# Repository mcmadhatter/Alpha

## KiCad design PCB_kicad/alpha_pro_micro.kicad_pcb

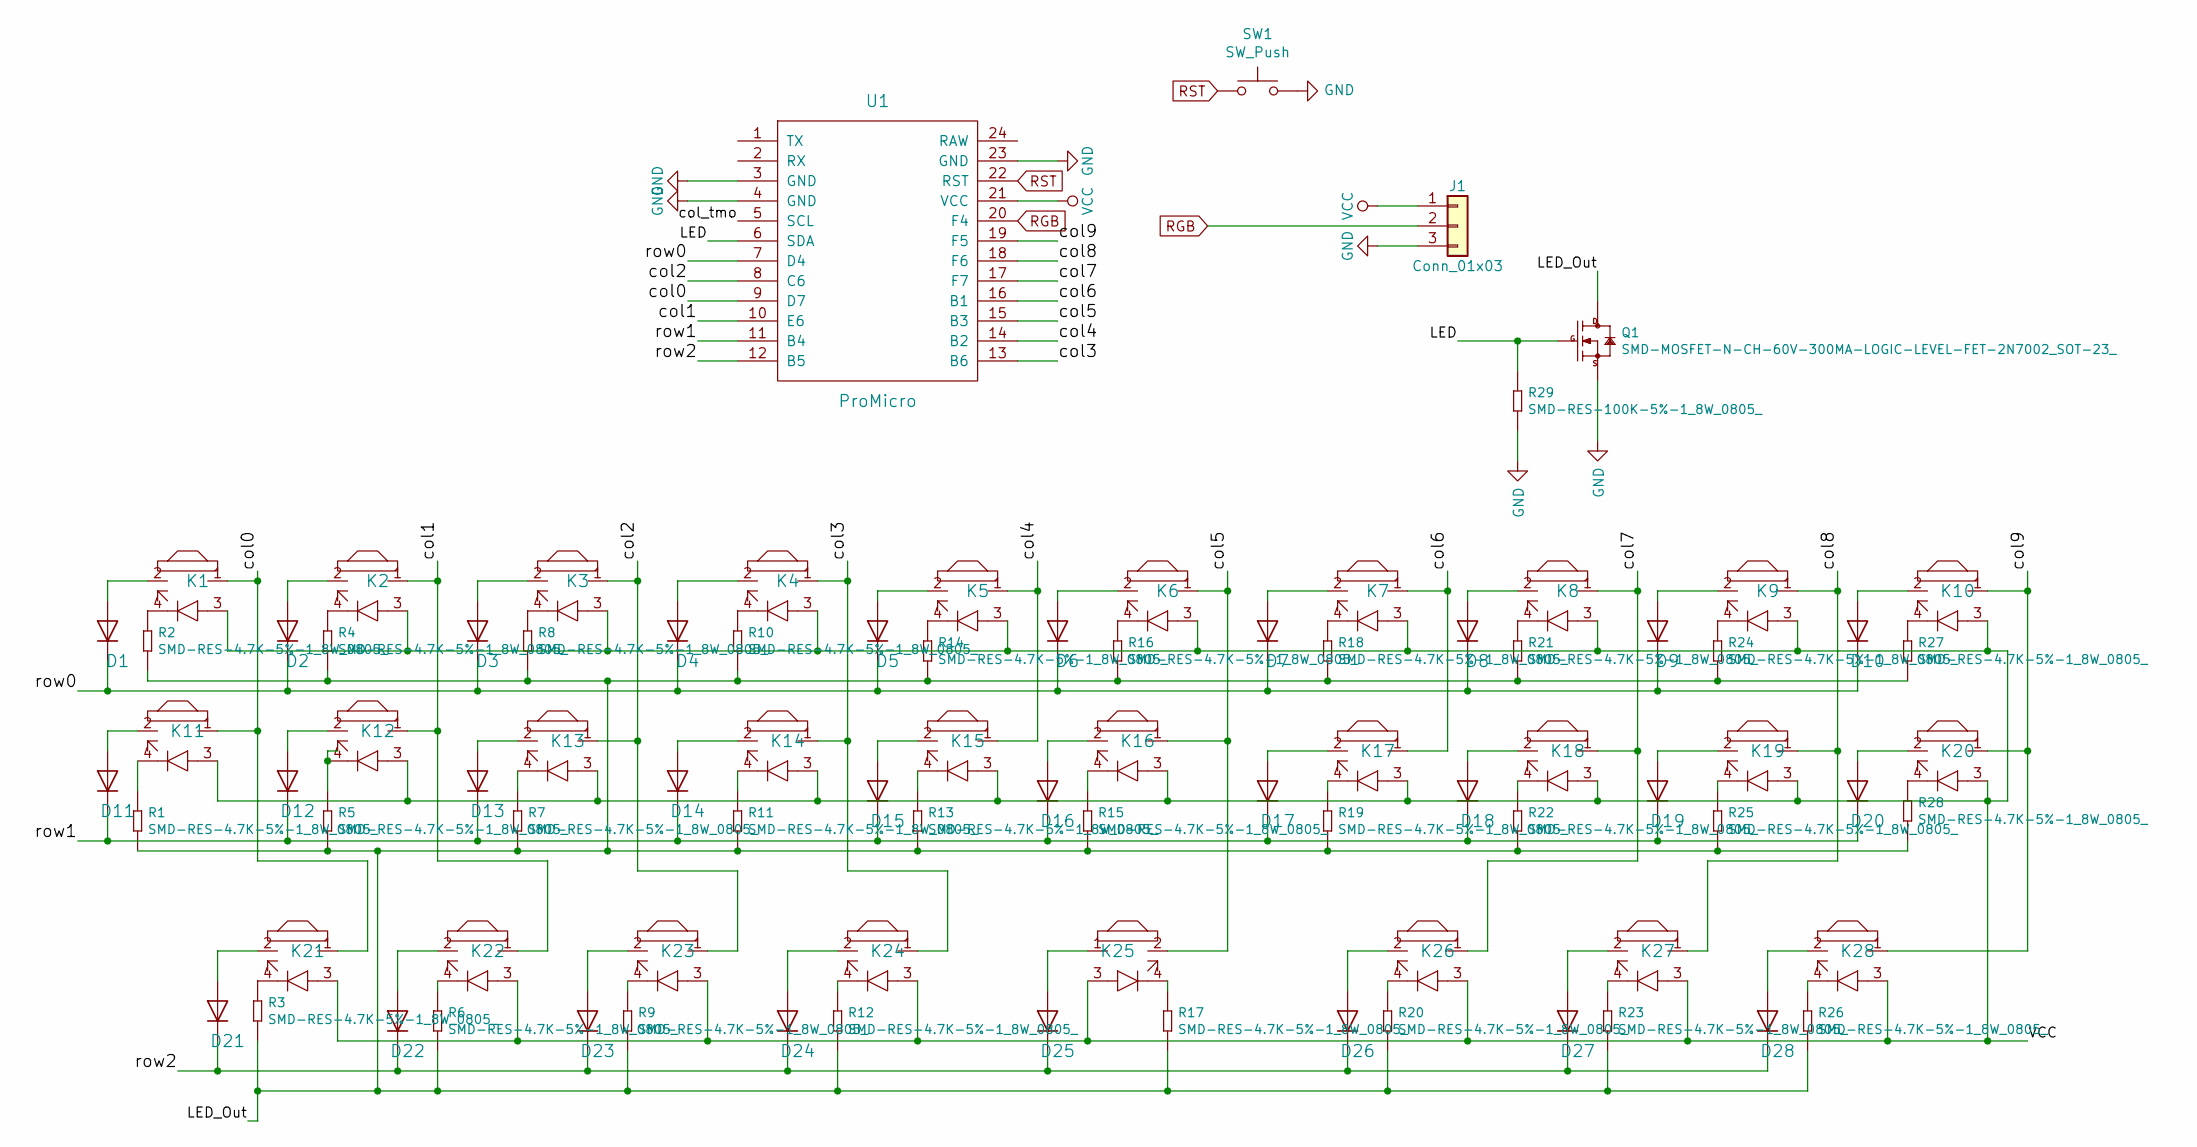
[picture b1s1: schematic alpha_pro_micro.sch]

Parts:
D1, D2, D3, D4, D5, D6, D7, D8, D9, D10, D11, D12, D13, D14, D15, D16, D17, D18, D19, D20, D21, D22, D23, D24, D25, D26, D27, D28: D; ComboDiode
J1: Conn_01x03; Pin_Header_Straight_1x03_Pitch2.54mm
K1, K2, K3, K4, K5, K6, K7, K8, K9, K10, K11, K12, K13, K14, K15, K16, K17, K18, K19, K20, K21, K22, K23, K24, K26, K27, K28: KEYSW; MXOnly-1U
K25: KEYSW; MX-Alps-Choc-2U-StabFlip
Q1: SMD-MOSFET-N-CH-60V-300MA-LOGIC-LEVEL-FET-2N7002_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; SOT-23; MPN 2N7002_215
R1, R2, R3, R4, R5, R6, R7, R8, R9, R10, R11, R12, R13, R14, R15, R16, R17, R18, R19, R20, R21, R22, R23, R24, R25, R26, R27, R28: SMD-RES-4.7K-5%-1_8W_0805_; PR-D1.8_L3.3MM; MPN RC0805JR-074K7L
R29: SMD-RES-100K-5%-1_8W_0805_; PR-D1.8_L3.3MM; MPN RC0805JR-074K7L
SW1: SW_Push; SKQG-1155865
U1: ProMicro

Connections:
/LED: Q1.1 (G), R29.2, U1.6 (SDA)
/LED_Out: Q1.3 (D), R1.1, R2.1, R3.1, R4.1, R5.1, R6.1, R7.1, R8.1, R9.1, R10.1, R11.1, R12.1, R13.1, R14.1, R15.1, R16.1, R17.1, R18.1, R19.1, R20.1, R21.1, R22.1, R23.1, R24.1, R25.1, R26.1, R27.1, R28.1
/col0: K1.1, K11.1, K21.1, U1.9 (D7)
/col1: K2.1, K12.1, K22.1, U1.10 (E6)
/col2: K3.1, K13.1, K23.1, U1.8 (C6)
/col3: K4.1, K14.1, K24.1, U1.13 (B6)
/col4: K5.1, K15.1, U1.14 (B2)
/col5: K6.1, K16.1, K25.2, U1.15 (B3)
/col6: K7.1, K17.1, U1.16 (B1)
/col7: K8.1, K18.1, K26.1, U1.17 (F7)
/col8: K9.1, K19.1, K27.1, U1.18 (F6)
/col9: K10.1, K20.1, K28.1, U1.19 (F5)
/col_tmo: U1.5 (SCL)
/row0: D1.1 (K), D2.1 (K), D3.1 (K), D4.1 (K), D5.1 (K), D6.1 (K), D7.1 (K), D8.1 (K), D9.1 (K), D10.1 (K), U1.7 (D4)
/row1: D11.1 (K), D12.1 (K), D13.1 (K), D14.1 (K), D15.1 (K), D16.1 (K), D17.1 (K), D18.1 (K), D19.1 (K), D20.1 (K), U1.11 (B4)
/row2: D21.1 (K), D22.1 (K), D23.1 (K), D24.1 (K), D25.1 (K), D26.1 (K), D27.1 (K), D28.1 (K), U1.12 (B5)
GND: J1.3, Q1.2 (S), R29.1, SW1.2, U1.3 (GND), U1.4 (GND), U1.23 (GND)
unnamed: D1.2 (A), K1.2
unnamed: D2.2 (A), K2.2
unnamed: D3.2 (A), K3.2
unnamed: D4.2 (A), K4.2
unnamed: D5.2 (A), K5.2
unnamed: D6.2 (A), K6.2
unnamed: D7.2 (A), K7.2
unnamed: D8.2 (A), K8.2
unnamed: D9.2 (A), K9.2
unnamed: D10.2 (A), K10.2
unnamed: D11.2 (A), K11.2
unnamed: D12.2 (A), K12.2
unnamed: D13.2 (A), K13.2
unnamed: D14.2 (A), K14.2
unnamed: D15.2 (A), K15.2
unnamed: D16.2 (A), K16.2
unnamed: D17.2 (A), K17.2
unnamed: D18.2 (A), K18.2
unnamed: D19.2 (A), K19.2
unnamed: D20.2 (A), K20.2
unnamed: D21.2 (A), K21.2
unnamed: D22.2 (A), K22.2
unnamed: D23.2 (A), K23.2
unnamed: D24.2 (A), K24.2
unnamed: D25.2 (A), K25.1
unnamed: D26.2 (A), K26.2
unnamed: D27.2 (A), K27.2
unnamed: D28.2 (A), K28.2
unnamed: K1.4, R2.2
unnamed: K2.4, R4.2
unnamed: K3.4, R8.2
unnamed: K4.4, R10.2
unnamed: K5.4, R14.2
unnamed: K6.4, R16.2
unnamed: K7.4, R18.2
unnamed: K8.4, R21.2
unnamed: K9.4, R24.2
unnamed: K10.4, R27.2
unnamed: K11.4, R1.2
unnamed: K12.4, R5.2
unnamed: K13.4, R7.2
unnamed: K14.4, R11.2
unnamed: K15.4, R13.2
unnamed: K16.4, R15.2
unnamed: K17.4, R19.2
unnamed: K18.4, R22.2
unnamed: K19.4, R25.2
unnamed: K20.4, R28.2
unnamed: K21.4, R3.2
unnamed: K22.4, R6.2
unnamed: K23.4, R9.2
unnamed: K24.4, R12.2
unnamed: K25.4, R17.2
unnamed: K26.4, R20.2
unnamed: K27.4, R23.2
unnamed: K28.4, R26.2
RGB: J1.2, U1.20 (F4)
RST: SW1.1, U1.22 (RST)
VCC: J1.1, K1.3, K2.3, K3.3, K4.3, K5.3, K6.3, K7.3, K8.3, K9.3, K10.3, K11.3, K12.3, K13.3, K14.3, K15.3, K16.3, K17.3, K18.3, K19.3, K20.3, K21.3, K22.3, K23.3, K24.3, K25.3, K26.3, K27.3, K28.3, U1.21 (VCC)

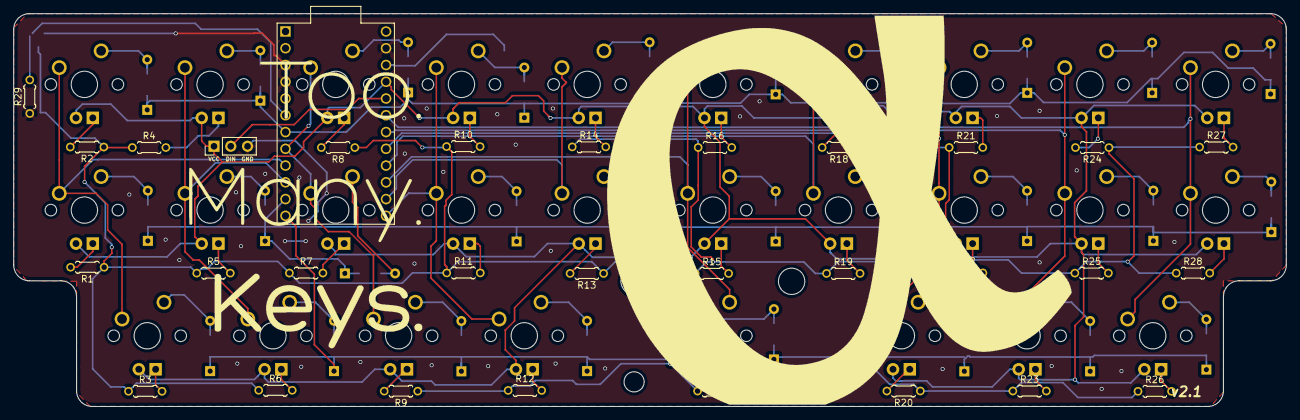
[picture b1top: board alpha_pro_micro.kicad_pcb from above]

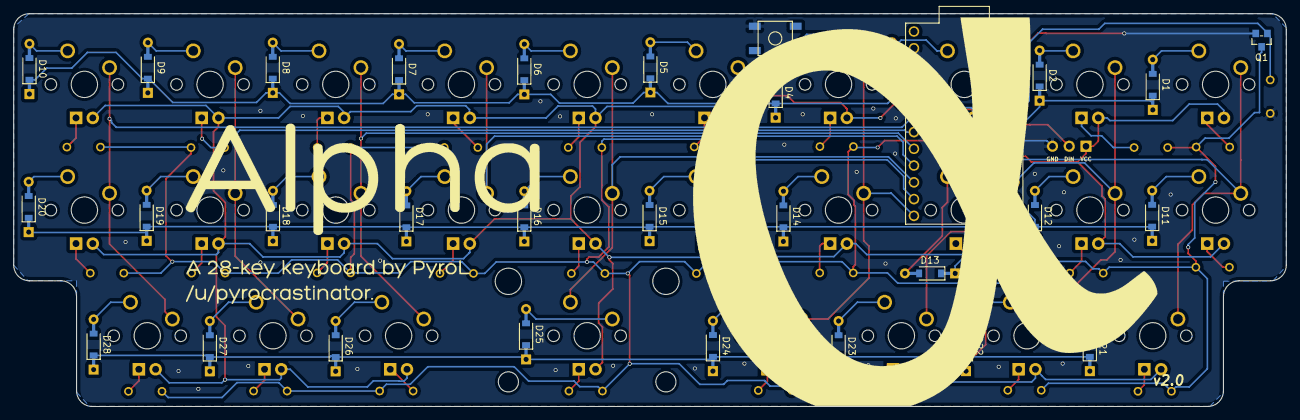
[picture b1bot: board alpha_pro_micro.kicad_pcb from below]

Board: 2 copper layers, 192.9 x 59.5 mm, 89 parts (2 on the bottom side), 75 nets.

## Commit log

2019-09-10 Swapped switch footprint
    Swapped switch footprint over to MX only, with LED support, and added support for LED driver and rest button.
